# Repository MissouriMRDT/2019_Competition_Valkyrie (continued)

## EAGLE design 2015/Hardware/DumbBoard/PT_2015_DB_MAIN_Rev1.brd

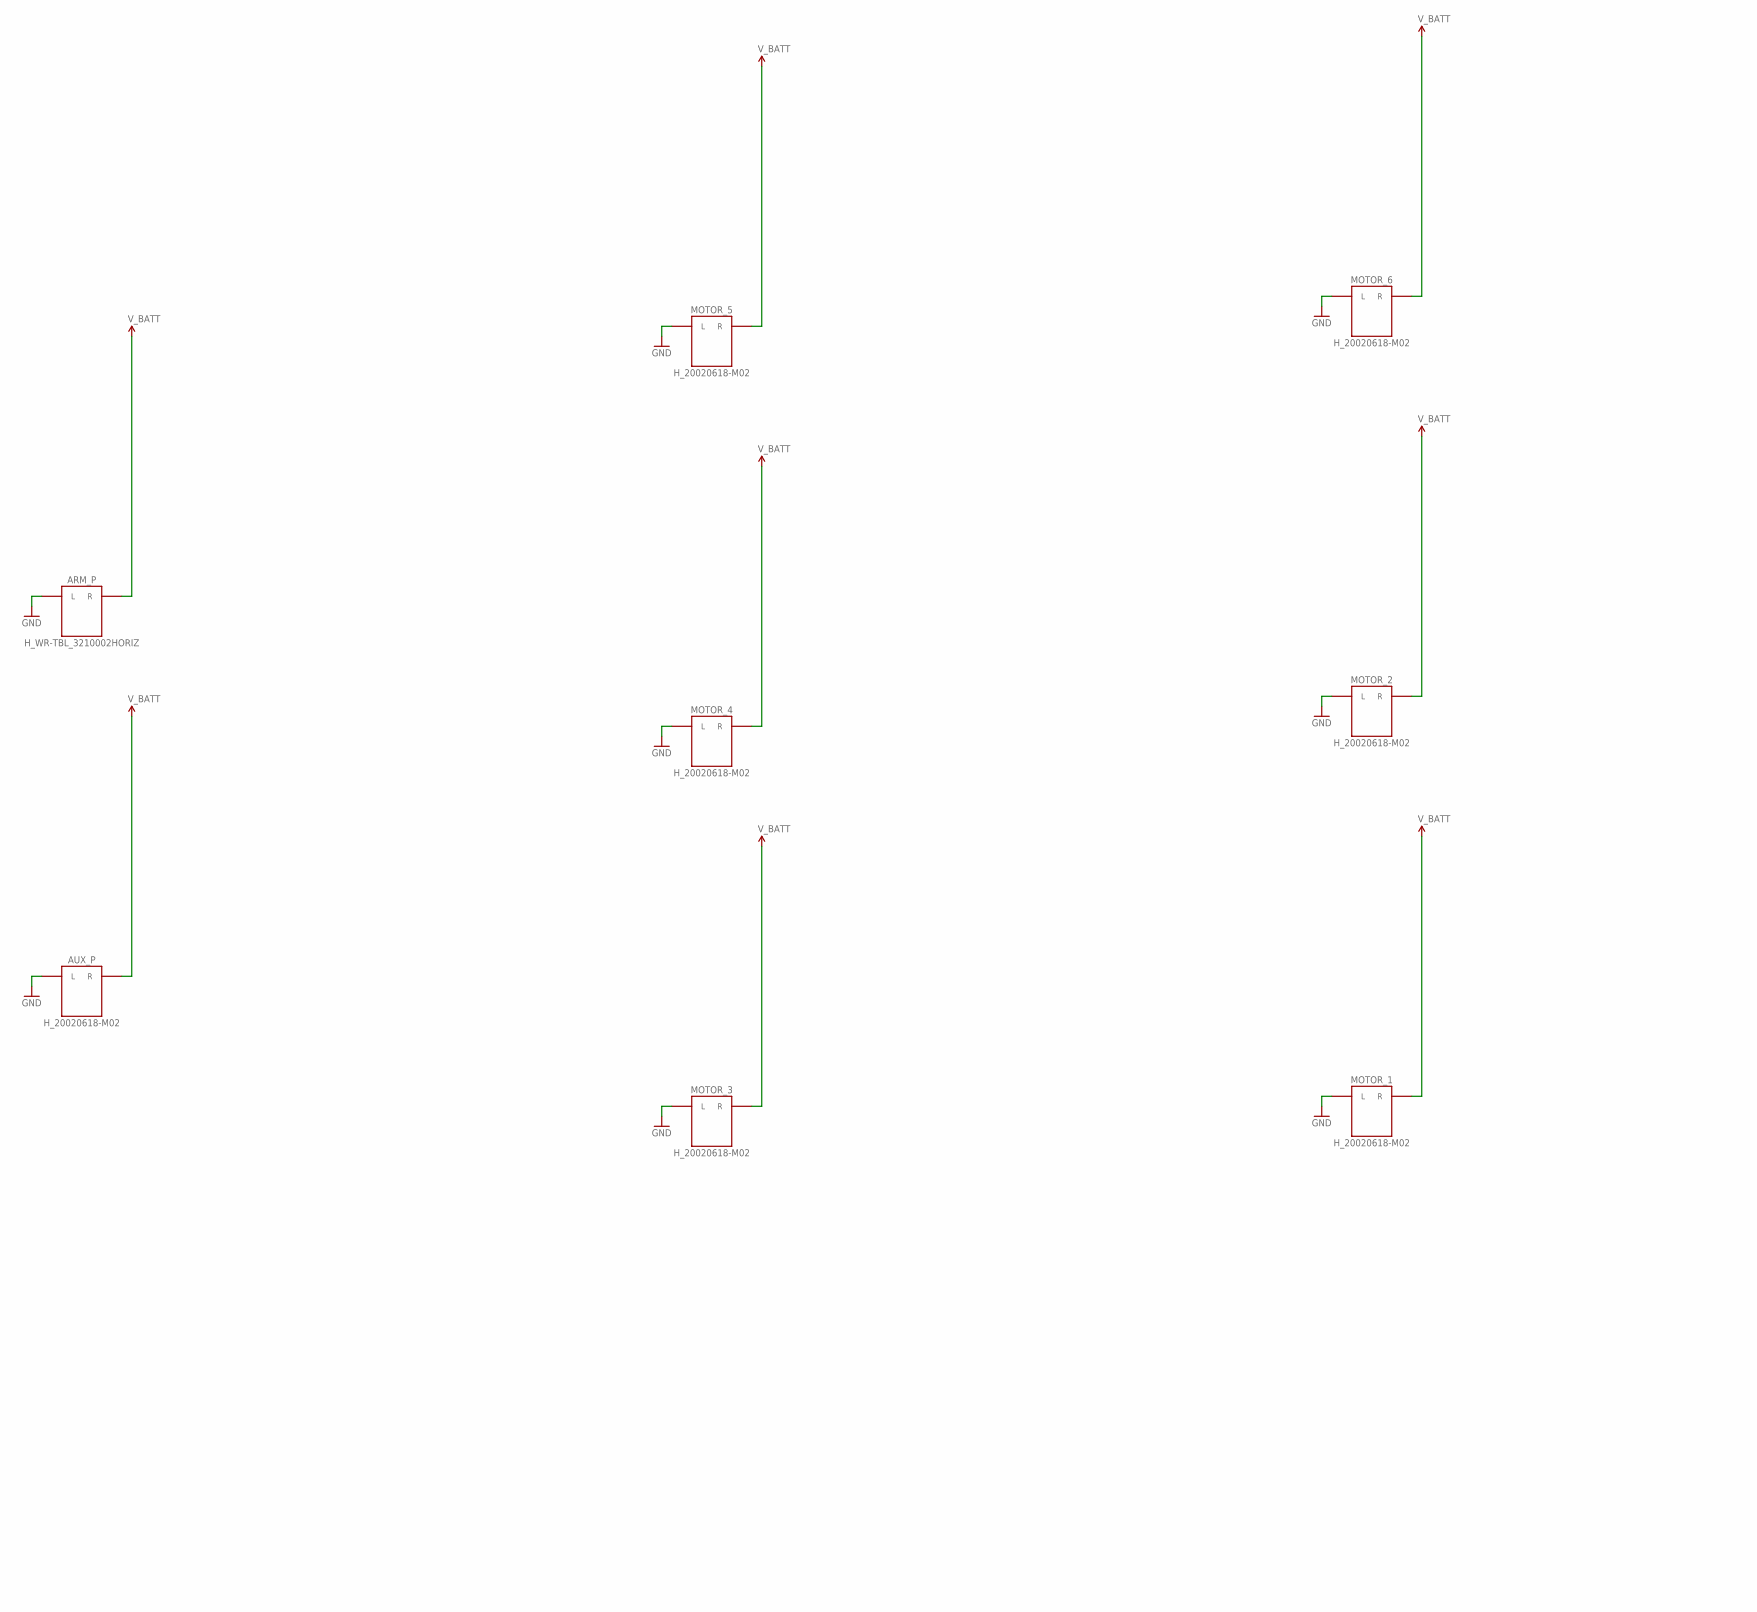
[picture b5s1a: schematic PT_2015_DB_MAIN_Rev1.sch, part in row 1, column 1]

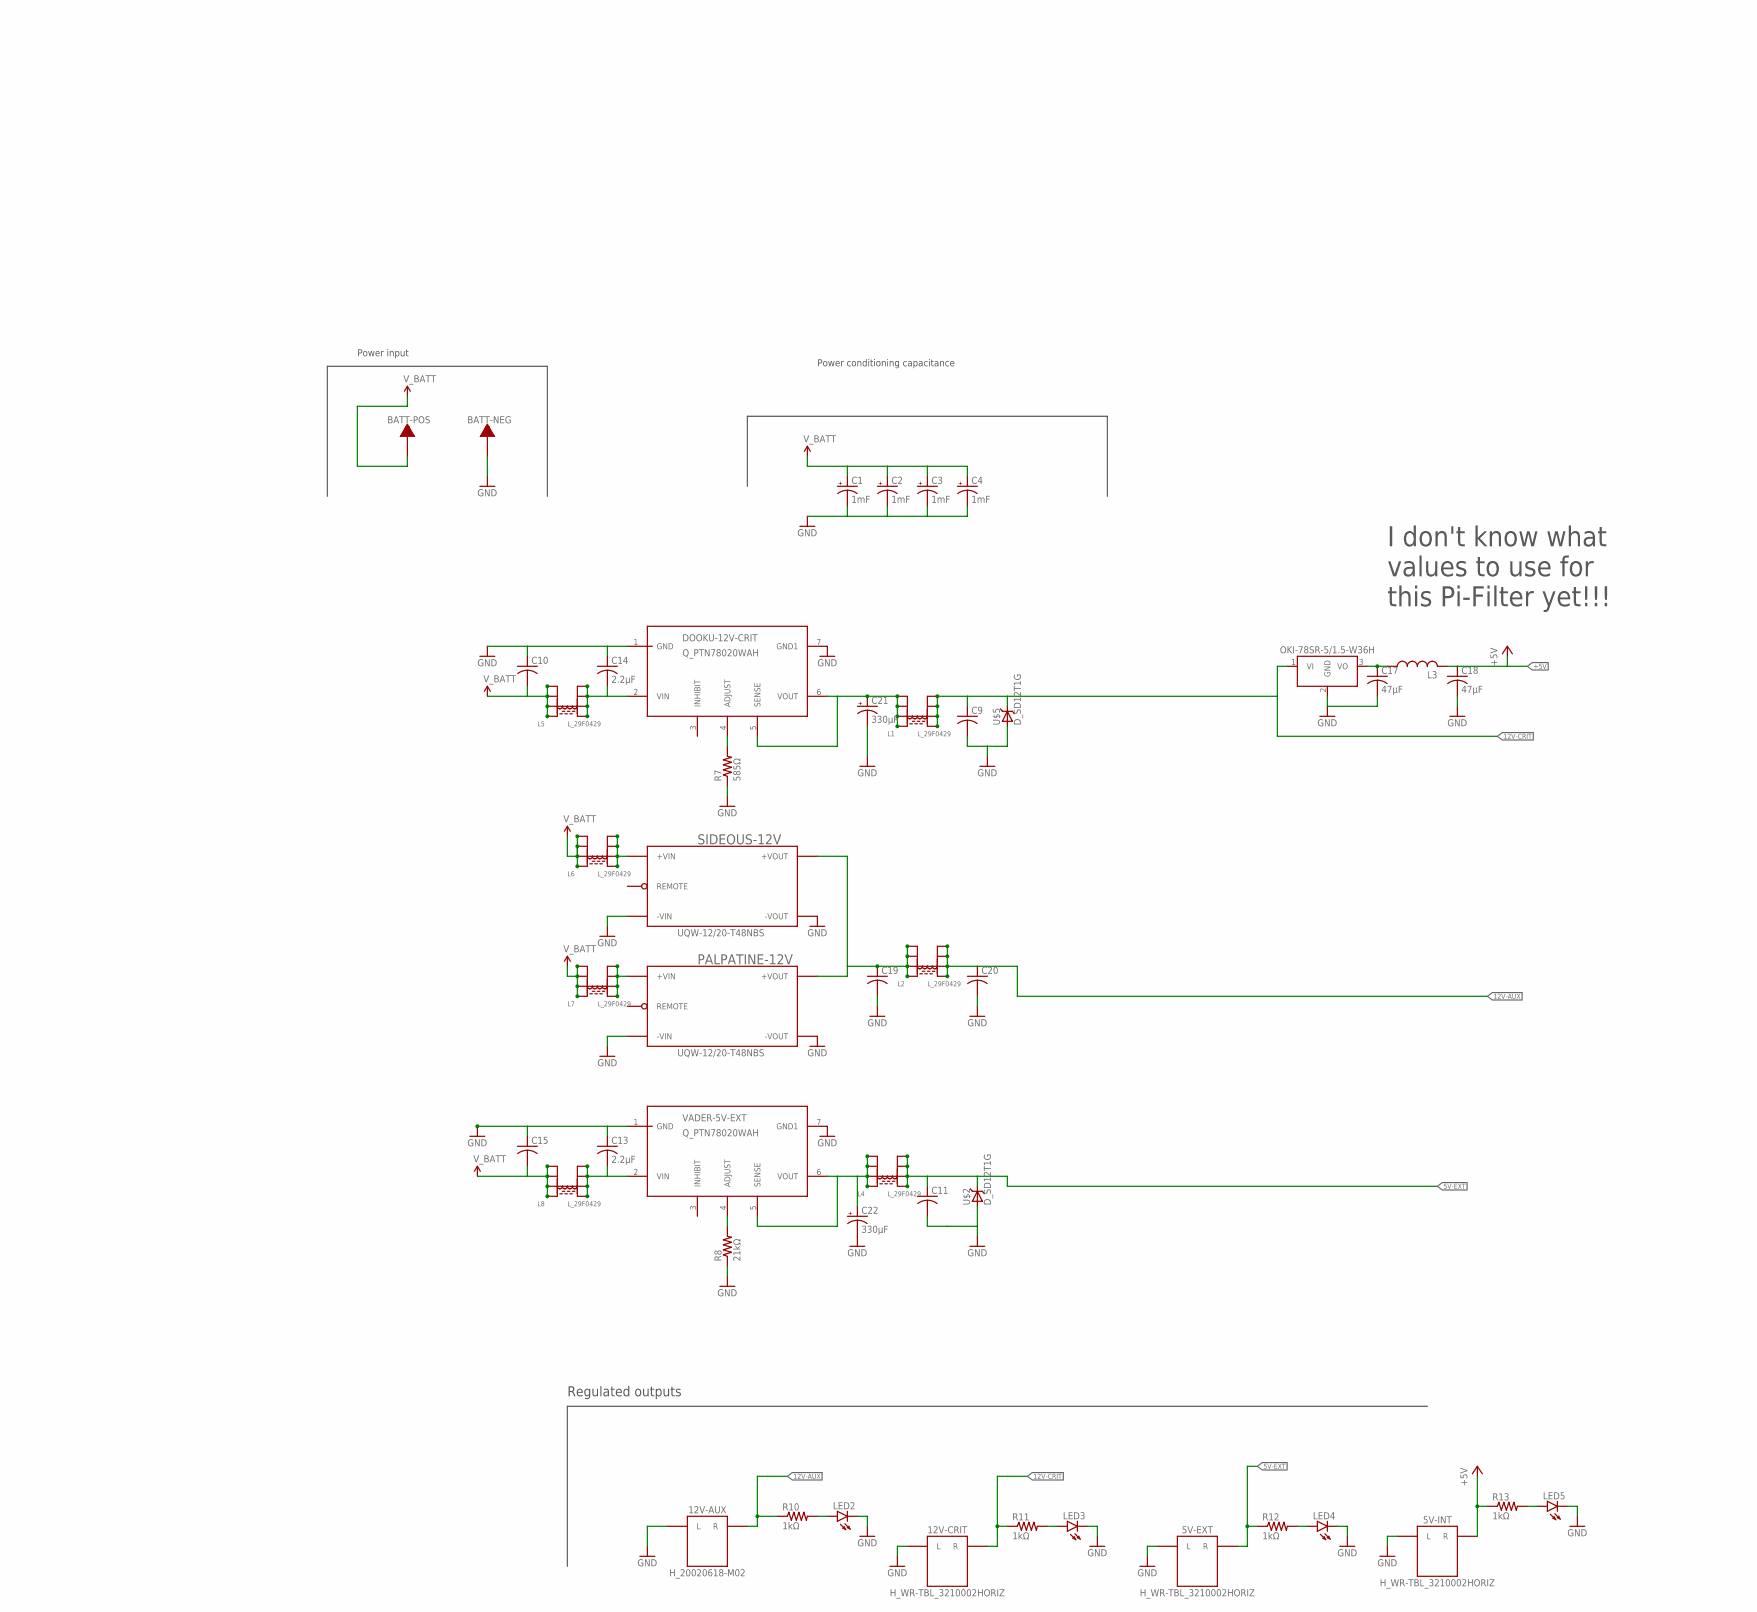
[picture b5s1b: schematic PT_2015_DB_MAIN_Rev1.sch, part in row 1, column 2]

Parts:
5V-EXT, 5V-INT, 12V-CRIT: H_WR-TBL_3210002HORIZ; 691322110002
12V-AUX: H_20020618-M02; 20020618-M02
ARM_P: H_WR-TBL_3210002HORIZ; 691322110002
AUX_P: H_20020618-M02; 20020618-M02
BATT-NEG: TERMINAL_HOLE; LARGE_TERMINAL_HOLE
BATT-POS: TERMINAL_HOLE; LARGE_TERMINAL_HOLE
C1, C2, C3, C4: 1mF; C_12.5MM
C9, C10, C11, C15, C19, C20: C-USC1206; C1206
C13, C14: 2.2µF; C1206
C17, C18: 47µF; C1206
C21, C22: 330µF; E5-8,5
DOOKU-12V-CRIT: Q_PTN78020WAH; R_PDSS-T7
L1, L2, L4, L5, L6, L7, L8: L_29F0429
L3: L-USL3216C; L3216C
LED2, LED3, LED4, LED5: LED1206; LED-1206
MOTOR_1, MOTOR_2, MOTOR_3, MOTOR_4, MOTOR_5, MOTOR_6: H_20020618-M02; 20020618-M02
OKI-78SR-5/1.5-W36H: Q_OKI-78SR; OKI-78SRH
PALPATINE-12V: UQW-12/20-T48NBS; U-T48-QB-NO_TRIM
R7: 585Ω; R1206
R8: 21kΩ; R1206
R10, R11, R12, R13: 1kΩ; 1206
SIDEOUS-12V: UQW-12/20-T48NBS; U-T48-QB-NO_TRIM
U$2, U$5: D_SD12T1G; SOD-323
VADER-5V-EXT: Q_PTN78020WAH; R_PDSS-T7

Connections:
5V-EXT: 5V-EXT.R, C11.1, L4.5, L4.6, L4.7, L4.8, R12.1, U$2.1 (C)
12V-AUX: 12V-AUX.R1 (R), 12V-AUX.R2 (R), C20.1, L2.5, L2.6, L2.7, L2.8, R10.1
12V-CRIT: 12V-CRIT.R, C9.1, L1.5, L1.6, L1.7, L1.8, OKI-78SR-5/1.5-W36H.1 (VI), R11.1, U$5.1 (C)
+5V: 5V-INT.R, C18.1, L3.2, R13.1
GND: 5V-EXT.L, 5V-INT.L, 12V-AUX.L1 (L), 12V-AUX.L2 (L), 12V-CRIT.L, ARM_P.L, AUX_P.L1 (L), AUX_P.L2 (L), BATT-NEG.P$1, C1.-, C2.-, C3.-, C4.-, C9.2, C10.1, C11.2, C13.1, C14.1, C15.1, C17.2, C18.2, C19.2, C20.2, C21.-, C22.-, DOOKU-12V-CRIT.1 (GND), DOOKU-12V-CRIT.7 (GND1), LED2.C, LED3.C, LED4.C, LED5.C, MOTOR_1.L1 (L), MOTOR_1.L2 (L), MOTOR_2.L1 (L), MOTOR_2.L2 (L), MOTOR_3.L1 (L), MOTOR_3.L2 (L), MOTOR_4.L1 (L), MOTOR_4.L2 (L), MOTOR_5.L1 (L), MOTOR_5.L2 (L), MOTOR_6.L1 (L), MOTOR_6.L2 (L), OKI-78SR-5/1.5-W36H.2 (GND), PALPATINE-12V.3 (-VIN), PALPATINE-12V.4 (-VOUT), R7.1, R8.1, SIDEOUS-12V.3 (-VIN), SIDEOUS-12V.4 (-VOUT), U$2.2 (A), U$5.2 (A), VADER-5V-EXT.1 (GND), VADER-5V-EXT.7 (GND1)
unnamed: C13.2, L8.5, L8.6, L8.7, L8.8, VADER-5V-EXT.2 (VIN)
unnamed: L7.5, L7.6, L7.7, L7.8, PALPATINE-12V.1 (+VIN)
unnamed: L6.5, L6.6, L6.7, L6.8, SIDEOUS-12V.1 (+VIN)
unnamed: C19.1, L2.1, L2.2, L2.3, L2.4, PALPATINE-12V.8 (+VOUT), SIDEOUS-12V.8 (+VOUT)
unnamed: C14.2, DOOKU-12V-CRIT.2 (VIN), L5.5, L5.6, L5.7, L5.8
unnamed: DOOKU-12V-CRIT.4 (ADJUST), R7.2
unnamed: C22.+, L4.1, L4.2, L4.3, L4.4, VADER-5V-EXT.5 (SENSE), VADER-5V-EXT.6 (VOUT)
unnamed: R8.2, VADER-5V-EXT.4 (ADJUST)
unnamed: C21.+, DOOKU-12V-CRIT.5 (SENSE), DOOKU-12V-CRIT.6 (VOUT), L1.1, L1.2, L1.3, L1.4
unnamed: LED2.A, R10.2
unnamed: LED3.A, R11.2
unnamed: LED4.A, R12.2
unnamed: LED5.A, R13.2
unnamed: C17.1, L3.1, OKI-78SR-5/1.5-W36H.3 (VO)
V_BATT: ARM_P.R, AUX_P.R1 (R), AUX_P.R2 (R), BATT-POS.P$1, C1.+, C2.+, C3.+, C4.+, C10.2, C15.2, L5.1, L5.2, L5.3, L5.4, L6.1, L6.2, L6.3, L6.4, L7.1, L7.2, L7.3, L7.4, L8.1, L8.2, L8.3, L8.4, MOTOR_1.R1 (R), MOTOR_1.R2 (R), MOTOR_2.R1 (R), MOTOR_2.R2 (R), MOTOR_3.R1 (R), MOTOR_3.R2 (R), MOTOR_4.R1 (R), MOTOR_4.R2 (R), MOTOR_5.R1 (R), MOTOR_5.R2 (R), MOTOR_6.R1 (R), MOTOR_6.R2 (R)

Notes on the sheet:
Power conditioning capacitance
Power input
I don't know what values to use for this Pi-Filter yet!!!
Regulated outputs

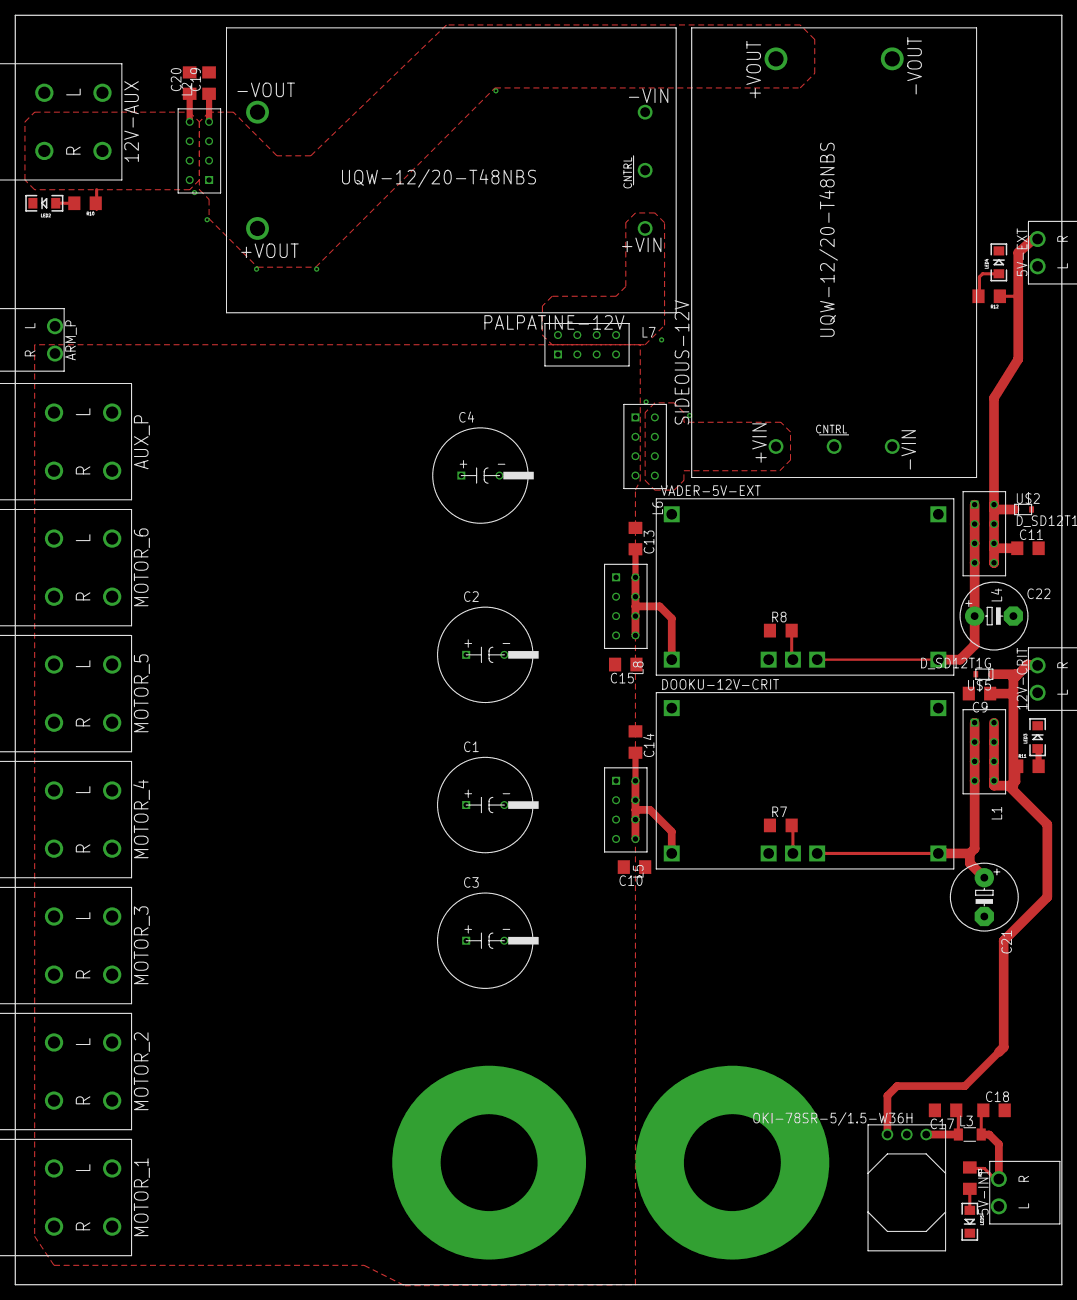
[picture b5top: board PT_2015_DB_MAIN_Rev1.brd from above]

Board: 2 copper layers, 137.2 x 166.4 mm, 55 parts (0 on the bottom side), 20 nets.

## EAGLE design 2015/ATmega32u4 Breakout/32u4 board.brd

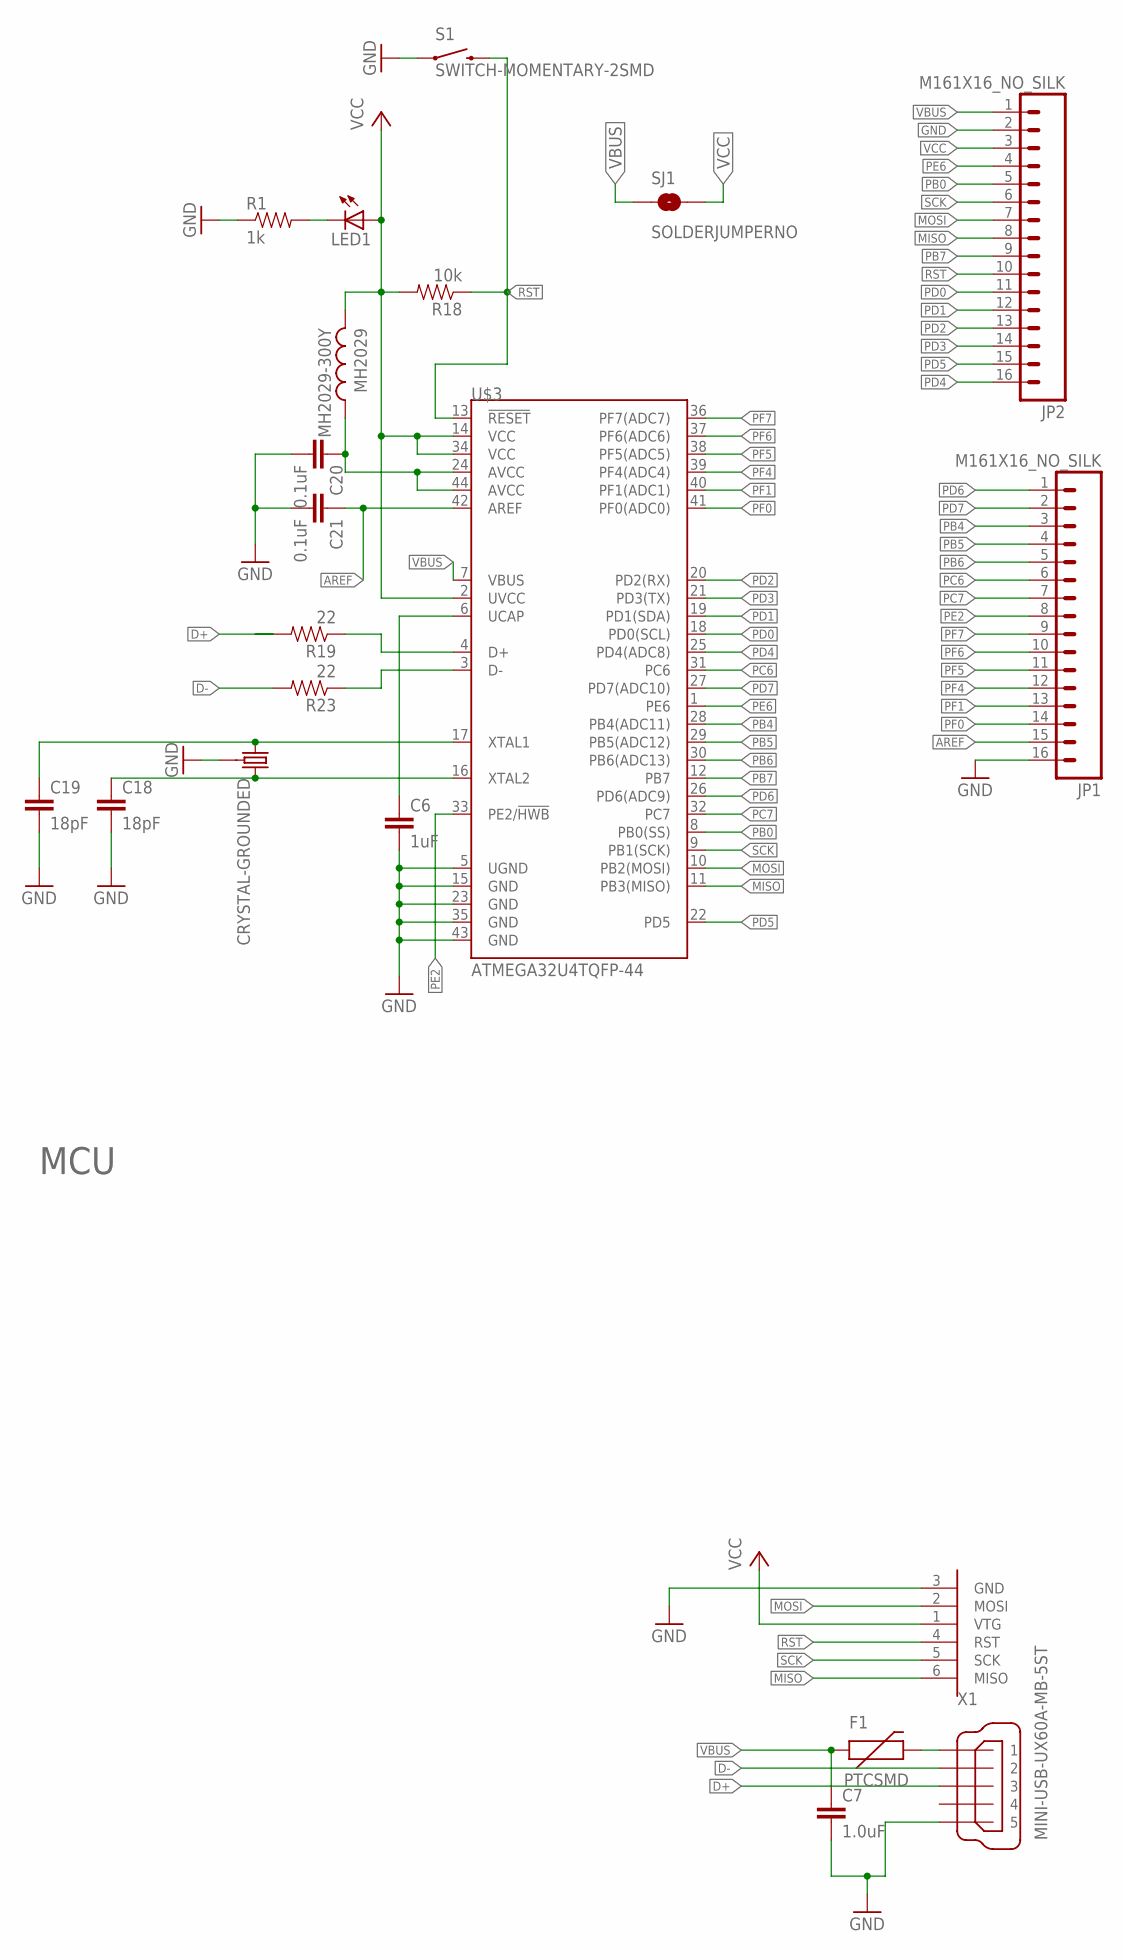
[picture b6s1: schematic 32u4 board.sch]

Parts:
C6: 1uF; 0603-CAP
C7: 1.0uF; 0603-CAP
C18, C19: 18pF; 0603-CAP
C20, C21: 0.1uF; 0603-CAP
F1: PTCSMD; PTC-1206
JP1, JP2: M161X16_NO_SILK; 1X16_NO_SILK
LED1: LEDCHIPLED_0603; CHIPLED_0603
MH2029: MH2029-300Y; L2012C
R1: 1k; 0603-RES
R18: 10k; 0603-RES
R19, R23: 22; 0603-RES
S1: SWITCH-MOMENTARY-2SMD; TACTILE_SWITCH_SMD
SJ1: SOLDERJUMPERNO; SJ_2S-NO
U$2: ICSP_SMD; ICSP
U$3: ATMEGA32U4TQFP-44; TQFP44
U$4: CRYSTAL-GROUNDED; CRYSTAL-SMD-5X3
X1: MINI-USB-UX60A-MB-5ST; UX60A-MB-5ST

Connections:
AREF: C21.1, JP1.15, U$3.42 (AREF)
D+: R19.2, X1.3
D-: R23.2, X1.2
GND: C6.2, C7.2, C18.2, C19.2, C20.2, C21.2, JP1.16, JP2.2, R1.1, S1.1, U$2.3 (GND), U$3.5 (UGND), U$3.15 (GND), U$3.23 (GND), U$3.35 (GND), U$3.43 (GND), U$4.2 (3), U$4.4 (3), X1.5
MISO: JP2.8, U$2.6 (MISO), U$3.11 (PB3(MISO))
MOSI: JP2.7, U$2.2 (MOSI), U$3.10 (PB2(MOSI))
unnamed: LED1.C, R1.2
unnamed: F1.2, X1.1
unnamed: R19.1, U$3.4 (D+)
unnamed: R23.1, U$3.3 (D-)
unnamed: C6.1, U$3.6 (UCAP)
unnamed: C20.1, MH2029.1, U$3.24 (AVCC), U$3.44 (AVCC)
unnamed: C19.1, U$3.17 (XTAL1), U$4.3 (1)
unnamed: C18.1, U$3.16 (XTAL2), U$4.1 (2)
PB0: JP2.5, U$3.8 (PB0(SS))
PB4: JP1.3, U$3.28 (PB4(ADC11))
PB5: JP1.4, U$3.29 (PB5(ADC12))
PB6: JP1.5, U$3.30 (PB6(ADC13))
PB7: JP2.9, U$3.12 (PB7)
PC6: JP1.6, U$3.31 (PC6)
PC7: JP1.7, U$3.32 (PC7)
PD0: JP2.11, U$3.18 (PD0(SCL))
PD1: JP2.12, U$3.19 (PD1(SDA))
PD2: JP2.13, U$3.20 (PD2(RX))
PD3: JP2.14, U$3.21 (PD3(TX))
PD4: JP2.16, U$3.25 (PD4(ADC8))
PD5: JP2.15, U$3.22 (PD5)
PD6: JP1.1, U$3.26 (PD6(ADC9))
PD7: JP1.2, U$3.27 (PD7(ADC10))
PE2: JP1.8, U$3.33 (PE2/!HWB)
PE6: JP2.4, U$3.1 (PE6)
PF0: JP1.14, U$3.41 (PF0(ADC0))
PF1: JP1.13, U$3.40 (PF1(ADC1))
PF4: JP1.12, U$3.39 (PF4(ADC4))
PF5: JP1.11, U$3.38 (PF5(ADC5))
PF6: JP1.10, U$3.37 (PF6(ADC6))
PF7: JP1.9, U$3.36 (PF7(ADC7))
RST: JP2.10, R18.1, S1.3 (2), U$2.4 (RST), U$3.13 (!RESET)
SCK: JP2.6, U$2.5 (SCK), U$3.9 (PB1(SCK))
VBUS: C7.1, F1.1, JP2.1, SJ1.1, U$3.7 (VBUS)
VCC: JP2.3, LED1.A, MH2029.2, R18.2, SJ1.2, U$2.1 (VTG), U$3.2 (UVCC), U$3.14 (VCC), U$3.34 (VCC)

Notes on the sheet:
MCU

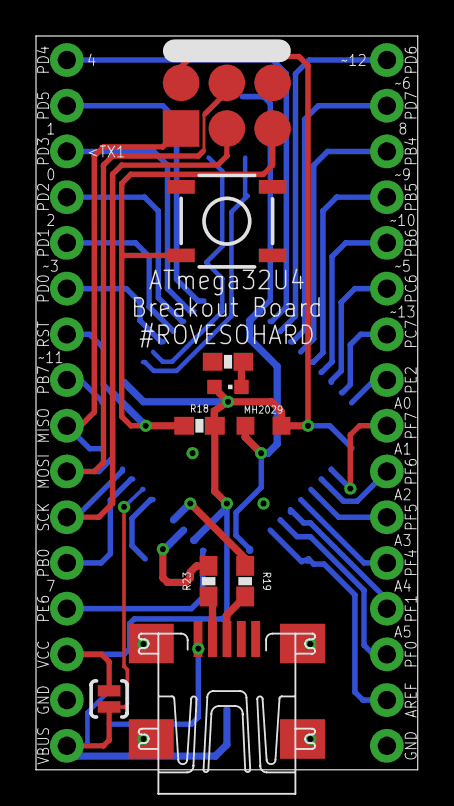
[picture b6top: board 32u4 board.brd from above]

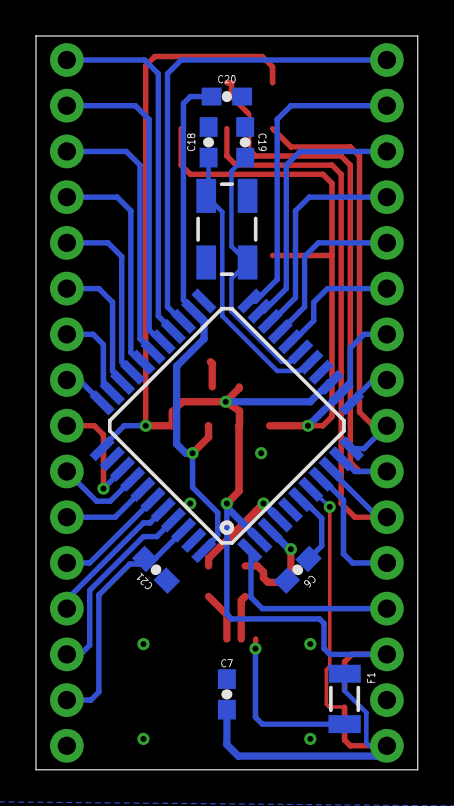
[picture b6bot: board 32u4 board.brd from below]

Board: 2 copper layers, 21.2 x 40.8 mm, 21 parts (9 on the bottom side), 41 nets.

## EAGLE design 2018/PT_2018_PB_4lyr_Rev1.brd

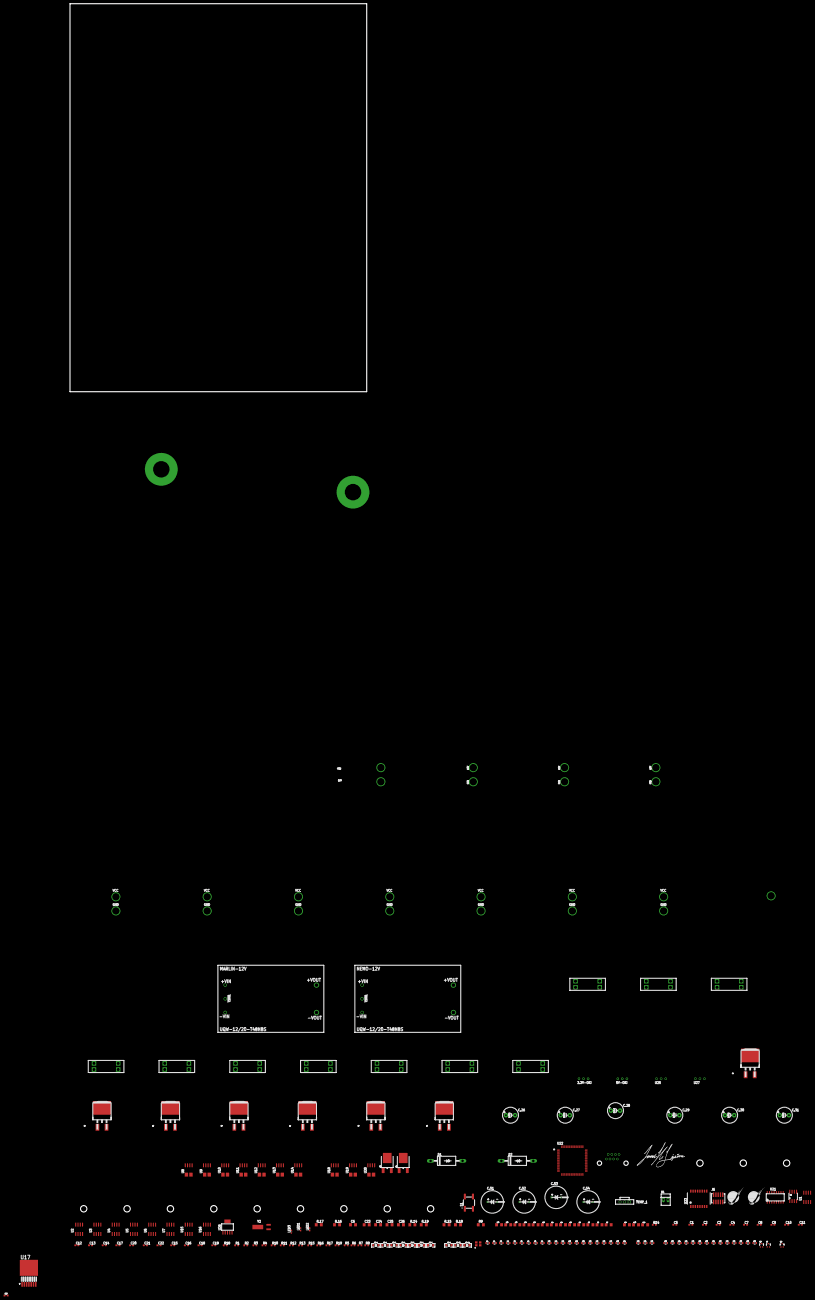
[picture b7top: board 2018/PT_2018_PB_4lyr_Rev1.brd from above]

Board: 4 copper layers, 220 parts (0 on the bottom side), 147 nets, no tracks yet.

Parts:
3.3V-OKI, 5V-OKI: Q_OKI-78SR; OKI-78SR_HORIZ
BATT-NEG: TERMINAL_HOLE; LARGE_TERMINAL_HOLE
BATT-POS: TERMINAL_HOLE; LARGE_TERMINAL_HOLE
C1, C2, C3, C4, C7, C8, C9, C10, C11, C12, C17, C20, C21: 0.1uF; C0603
C5: 1000pF; C0603
C6: 4700pF; C1206
C13: 1.0uF; C0603
C14, C22: 2.2uF; C0603
C15, C16, C18, C19: 12pF; C0603
C23, C24, C25, C26: 10uF; C1206
C27: 10pF; 0603
C.1, C.2, C.3, C.4, C.5, C.6, C.7, C.39, C.40, C.41, C.42, C.43, C.44: 1nF; 0805
C.8, C.9, C.10, C.11, C.12, C.13, C.14, C.15, C.16, C.17, C.18, C.19, C.20, C.21, C.23, C.24, C.25: .1µF; 0805
C.26, C.27, C.28, C.29, C.30, C.31: 330µF; E5-8,5
C.35, C.36, C.37: 2.2uF; 1206
C.45, C.46, C.47: 10uF; 1206
C.48, C.49, C.50: .1uF; 0805
C.51, C.52, C.53, C.54: 1mF; C_12.5MM
C.55, C.56, C.57, C.58, C.59: .1u; 0805
D1, D2: 1.5KE36A; CB429-17
J1, J2, J3: APP_2POS_CONFIG12V_VERT; APP45_12V_VERT_CONFIG
J5: RJ45KEYSTONE-942; KEYSTONE-942
J6: JTAG_ARM_10PIN; CON_2X5_50MIL
J7: APP_2POS_CONFIG12V_HORIZ; APP45_12V_HORIZ_CONFIG
J8: APPPP45_PCB_HORIZ_RIGHT; APP45_PCB_HORIZ_RIGHT
LED1, LED2: GREEN; CHIP-LED0603
LED3: ORANGE; CHIP-LED0603
LED-1, LED-2, LED-3, LED-4, LED-5, LED-6, LED-7, LED-9, LED-10, LED-11: LED-1206
MARLIN-12V: UQW-12/20-T48NBS; U-T48-QB-NO_TRIM
NEMO-12V: UQW-12/20-T48NBS; U-T48-QB-NO_TRIM
Q1, Q2, Q3, Q4, Q5, Q6, Q7: Q_IRFS7437PbF; D2PACK
Q8, Q12: 2N7002; SOT323
Q10, Q11: MOSFET-NCHANNELFDD8780; DPAK
Q13: 2N7002PW; SOT323
R1, R3, R4: 49.9; R0603
R2: 49.4; R0603
R5, R6, R7, R8: 75; R0603
R9: 1M; R1206
R10, R11, R19: 330; R0603
R12: 1M; R0603
R13: 51; R0603
R14: 4.87k 1%; R0603
R15: 2k; R0603
R16: 100; R0603
R17: 10k; R0603
R18: 100k; R0603
R.1, R.2, R.3, R.4, R.5, R.6, R.7: 5kΩ; 1206
R.9, R.10, R.11: 1kΩ; 1206
R.14, R.19: 100k; R1206
R.15, R.18: 1k; R1206
R.16: 100k 1%; R1206
R.17: 10kΩ 1%; R1206
S1: SWITCH_TACTILE; SWITCH_6MM_6MM_TE_CON_SMD
TEMP_1: SL03; MOLEX-70543-0002
U1, U2, U3, U4, U5, U6, U7, U15, U16: LT1910; SO8
U8, U9, U10, U11, U12, U13, U14, U18, U19, U20: ACS722LLCTR-40AU-T; SOIC8_ACS711
U17: LM2678S-3.3; TO127P1435X457-8N
U21: MAX3232D; SOIC16
U22: TM4C1294NCPDT; TQFP-128
U23: HX1198FNL
U24: SLVU2.8-4; SOIC8
U25, U27: OKI-78SR-5/1.5-W36HC; OKI-78SR_HORIZ
U26: TPS73733DCQ; SOT-223-6
U$2: JACOB_SIG
U$3, U$7, U$15, U$19, U$20, U$22, U$23: APP_2POS_CONFIGMOCO_VERT; APP45_MOCO_VERT_CONFIG
U$4, U$41: MRDT_LOGO
U$5, U$6, U$8, U$9, U$10, U$11, U$12, U$16, U$34, U$35, U$39, U$40: MOUNTING_HOLE#6; #6_SCREW
U$26, U$27, U$28, U$29, U$30, U$31, U$32, U$36, U$37, U$38: ATC_FUSE_BLOCK; BLOCK_3557-2
X1: 22-23-2021
Y1: NX3225GA; NDK3.2X2.5
Y2: CRYATL_32K_SMD; CRYSTAL_32K_SMD

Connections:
3.3V: 3.3V-OKI.3, C.8.2, C.9.2, C.10.2, C.11.2, C.12.2, C.13.2, C.14.2, C.23.2, C.24.2, C.25.2, C.43.1, C.46.1, C.49.1, C.55.1, U8.8, U9.8, U10.8, U11.8, U12.8, U13.8, U14.8, U18.8, U19.8, U20.8, U21.16
5V: 5V-OKI.3, C.42.1, C.45.1, C.48.1, X1.2
12V-AUX-ACT: J3.VCC, R.9.1, U18.4
12V-AUX-COM: J1.VCC, R.10.1, U20.4
12V-AUX-LOGIC: J2.VCC, R.11.1, U19.4
232_RX: TEMP_1.2, U21.13
232_TX: TEMP_1.3, U21.14
!RESET: J6.P10, R16.2, S1.P$3, S1.P$4
+3V3: C1.1, C2.1, C3.1, C4.1, C8.1, C9.1, C10.1, C11.1, C22.1, J6.P1, LED3.A, R1.1, R2.1, R3.1, R4.1, R12.2, R13.2, R17.1, U22.P$7, U22.P$8, U22.P$9, U22.P$16, U22.P$26, U22.P$28, U22.P$39, U22.P$47, U22.P$51, U22.P$52, U22.P$69, U22.P$79, U22.P$90, U22.P$101, U22.P$113, U22.P$122, U23.P$2, U23.P$7, U26.2
+5V_ACT: C26.1, U27.3
+5V_LOGIC: C20.1, C24.1, R18.1, U25.3, U26.1
+12V_ACT: C25.1, J8.P$1, U27.1
+12V_LOGIC: C23.1, J7.12V, U25.1
ACT-CTL: R.18.2, U22.P$109
ACT-SIG: U15.4, U22.P$31
ACT/COM-CTL: R.15.2, U22.P$103
COM-SIG: U16.4, U22.P$81
DRAIN-M1: C.15.2, Q1.TAB, U1.6, U1.8, U8.4
DRAIN-M2: C.16.2, Q2.TAB, U2.6, U2.8, U9.4
DRAIN-M3: C.17.2, Q3.TAB, U3.6, U3.8, U10.4
DRAIN-M4: C.18.2, Q4.TAB, U4.6, U4.8, U11.4
DRAIN-M5: C.19.2, Q5.TAB, U5.6, U5.8, U12.4
DRAIN-M6: C.20.2, Q6.TAB, U6.6, U6.8, U13.4
DRAIN-M7: C.21.2, Q7.TAB, U7.6, U7.8, U14.4
EN0LED0: LED1.A, U22.P$42
EN0LED1: LED2.A, U22.P$46
EN0RXI_N: R4.2, U22.P$53, U23.P$8
EN0RXI_P: R3.2, U22.P$54, U23.P$6
EN0TXO_N: R2.2, U22.P$56, U23.P$3
EN0TXO_P: R1.2, U22.P$57, U23.P$1
FAN_CTL_1: Q13.1, U22.P$3
FILTER-M1: C.1.1, U8.6
FILTER-M2: C.2.1, U9.6
FILTER-M3: C.3.1, U10.6
FILTER-M4: C.4.1, U11.6
FILTER-M5: C.5.1, U12.6
FILTER-M6: C.6.1, U13.6
FILTER-M7: C.7.1, U14.6
GATE-M1: Q1.1, U1.5
GATE-M2: Q2.1, U2.5
GATE-M3: Q3.1, U3.5
GATE-M4: Q4.1, U4.5
GATE-M5: Q5.1, U5.5
GATE-M6: Q6.1, U6.5
GATE-M7: Q7.1, U7.5
GND: 3.3V-OKI.2, 5V-OKI.2, BATT-NEG.P$1, C1.2, C2.2, C3.2, C4.2, C6.2, C7.2, C8.2, C9.2, C10.2, C11.2, C12.2, C13.2, C14.2, C15.2, C16.2, C17.2, C18.2, C19.2, C20.2, C21.2, C22.2, C23.2, C24.2, C25.2, C26.2, C.1.2, C.2.2, C.3.2, C.4.2, C.5.2, C.6.2, C.7.2, C.8.1, C.9.1, C.10.1, C.11.1, C.12.1, C.13.1, C.14.1, C.15.1, C.16.1, C.17.1, C.18.1, C.19.1, C.20.1, C.21.1, C.23.1, C.24.1, C.25.1, C.26.-, C.27.-, C.28.-, C.29.-, C.30.-, C.31.-, C.35.2, C.36.2, C.37.2, C.39.2, C.40.2, C.41.2, C.42.2, C.43.2, C.44.2, C.45.2, C.46.2, C.47.2, C.48.2, C.49.2, C.50.2, C.51.-, C.52.-, C.53.-, C.54.-, C.55.2, C.58.2, C.59.2, D1.A, D2.A, J1.GND, J2.GND, J3.GND, J6.P3, J6.P5, J7.GND, LED-1.C, LED-2.C, LED-3.C, LED-4.C, LED-5.C, LED-6.C, LED-7.C, LED-9.C, LED-10.C, LED-11.C, MARLIN-12V.3, MARLIN-12V.4, NEMO-12V.3, NEMO-12V.4, Q8.2, Q12.2, Q13.2, R9.1, R10.2, R11.2, R14.1, R19.2, R.14.2, R.17.1, R.19.2, S1.P$1, S1.P$2, TEMP_1.1, U1.1, U2.1, U3.1, U4.1, U5.1, U6.1, U7.1, U8.5, U9.5, U10.5, U11.5, U12.5, U13.5, U14.5, U15.1, U16.1, U17.8, U18.5, U19.5, U20.5, U21.15, U22.P$10, U22.P$17, U22.P$48, U22.P$55, U22.P$58, U22.P$80, U22.P$114, U25.2, U26.3, U26.6, U27.2, U$3.GND, U$7.GND, U$15.GND, U$19.GND, U$20.GND, U$22.GND, U$23.GND
IMEAS-ACT: U20.7, U22.P$13
IMEAS-COM: U19.7, U22.P$15
IMEAS-LOGIC: U18.7, U22.P$14
IMEAS-M1: U8.7, U22.P$21
IMEAS-M2: U9.7, U22.P$20
IMEAS-M3: U10.7, U22.P$19
IMEAS-M4: U11.7, U22.P$125
IMEAS-M5: U12.7, U22.P$18
IMEAS-M6: U13.7, U22.P$120
IMEAS-M7: U14.7, U22.P$121
LEDLINE-M1: LED-1.A, R.1.2
LEDLINE-M2: LED-2.A, R.2.2
LEDLINE-M3: LED-3.A, R.3.2
LEDLINE-M4: LED-4.A, R.4.2
LEDLINE-M5: LED-5.A, R.5.2
LEDLINE-M6: LED-6.A, R.6.2
LEDLINE-M7: LED-7.A, R.7.2
unnamed: C.26.+, NEMO-12V.8, U$30.IN_1, U$30.IN_2
unnamed: C27.2, U17.3
unnamed: MARLIN-12V.2, Q12.3
unnamed: C.41.1, U20.6
unnamed: C27.1, U17.1
unnamed: LED-9.A, R.9.2
unnamed: LED-11.A, R.11.2
unnamed: NEMO-12V.2, Q8.3
unnamed: C.28.+, C.29.+, C.30.+, C.31.+, C.36.1, C.37.1, MARLIN-12V.8, U$31.IN_1, U$31.IN_2, U$32.IN_1, U$32.IN_2
unnamed: C.58.1, U21.2
unnamed: C.39.1, U18.6
unnamed: C.40.1, U19.6
unnamed: LED-10.A, R.10.2
unnamed: Q11.1, U16.5
unnamed: C.27.+, C.35.1, U18.1, U$30.OUT_1, U$30.OUT_2
unnamed: Q11.3, U19.1
unnamed: Q11.4, U16.6, U16.8, U$31.OUT_1, U$31.OUT_2
unnamed: Q10.4, U15.6, U15.8, U$32.OUT_1, U$32.OUT_2
unnamed: Q10.3, U20.1
unnamed: Q8.1, R.18.1, R.19.1
unnamed: Q10.1, U15.5
unnamed: C.56.1, U21.1
unnamed: C.56.2, U21.3
unnamed: C.57.1, U21.4
unnamed: C.57.2, U21.5
unnamed: C.59.1, U21.6
unnamed: Q13.3, X1.1
unnamed: Q12.1, R.14.1, R.15.1
N_$1: R5.2, U23.P$15
N_$3: R6.2, U23.P$10
N_$4: J5.P$7, U23.P$14, U24.2, U24.7
N_$5: J5.P$6, U23.P$11, U24.3, U24.6
N_$6: J5.P$8, U23.P$16, U24.1, U24.8
N_$7: J5.P$3, U23.P$9, U24.4, U24.5
N_$8: LED2.C, R11.1
N_$9: LED1.C, R10.1
N_$10: C7.1, R13.1, U22.P$68
N_$11: J5.P$4, J5.P$5, R7.2
N_$12: R12.1, U22.P$64
N_$13: J5.P$1, J5.P$2, R8.2
N_$14: C5.1, R5.1, R6.1, R7.1, R8.1
N_$15: C5.2, C6.1, R9.2
N_$16: C12.1, C13.1, C14.1, U22.P$87, U22.P$115
N_$17: R15.2, U22.P$89
N_$18: C16.1, U22.P$88, Y1.P$3
N_$19: R14.2, U22.P$59
N_$20: C17.1, R16.1, R17.2, U22.P$70
N_$21: C15.1, R15.1, Y1.P$1
N_$22: C18.1, U22.P$67, Y2.P$2
N_$23: C19.1, U22.P$66, Y2.P$1
N_$25: R18.2, U26.5
N_$26: LED3.C, R19.1
N_$27: C21.1, U26.4
RX: J6.P7, U22.P$33
SER_RX: U21.12, U22.P$25
SER_TX: U21.11, U22.P$24
SIG-M1: U1.4, U22.P$106
SIG-M2: U2.4, U22.P$41
SIG-M3: U3.4, U22.P$29
SIG-M4: U4.4, U22.P$104
SIG-M5: U5.4, U22.P$30
SIG-M6: U6.4, U22.P$61
SIG-M7: U7.4, U22.P$60
SOURCE-M1: Q1.2, R.1.1, U$3.VCC
SOURCE-M2: Q2.2, R.2.1, U$23.VCC
SOURCE-M3: Q3.2, R.3.1, U$7.VCC
SOURCE-M4: Q4.2, R.4.1, U$15.VCC
SOURCE-M5: Q5.2, R.5.1, U$19.VCC
SOURCE-M6: Q6.2, R.6.1, U$20.VCC
SOURCE-M7: Q7.2, R.7.1, U$22.VCC
TARGET_TCK/SWCLK: J6.P4, U22.P$100
TARGET_TDI: J6.P8, U22.P$98
TARGET_TDO/SWO: J6.P6, U22.P$97
TARGET_TMS/SWDIO: J6.P2, U22.P$99
TX: J6.P9, U22.P$34
VMEAS-VBATT: R.16.1, R.17.2, U22.P$124
V_BATT: 3.3V-OKI.1, 5V-OKI.1, BATT-POS.P$1, C.44.1, C.47.1, C.50.1, C.51.+, C.52.+, C.53.+, C.54.+, D1.C, D2.C, MARLIN-12V.1, NEMO-12V.1, R.16.2, U17.2, U$26.IN_1, U$26.IN_2, U$27.IN_1, U$27.IN_2, U$28.IN_1, U$28.IN_2, U$29.IN_1, U$29.IN_2, U$36.IN_1, U$36.IN_2, U$37.IN_1, U$37.IN_2, U$38.IN_1, U$38.IN_2
V_BATT_M1: U8.1, U$26.OUT_1, U$26.OUT_2
V_BATT_M2: U9.1, U$27.OUT_1, U$27.OUT_2
V_BATT_M3: U10.1, U$36.OUT_1, U$36.OUT_2
V_BATT_M4: U11.1, U$37.OUT_1, U$37.OUT_2
V_BATT_M5: U12.1, U$38.OUT_1, U$38.OUT_2
V_BATT_M6: U13.1, U$29.OUT_1, U$29.OUT_2
V_BATT_M7: U14.1, U$28.OUT_1, U$28.OUT_2
